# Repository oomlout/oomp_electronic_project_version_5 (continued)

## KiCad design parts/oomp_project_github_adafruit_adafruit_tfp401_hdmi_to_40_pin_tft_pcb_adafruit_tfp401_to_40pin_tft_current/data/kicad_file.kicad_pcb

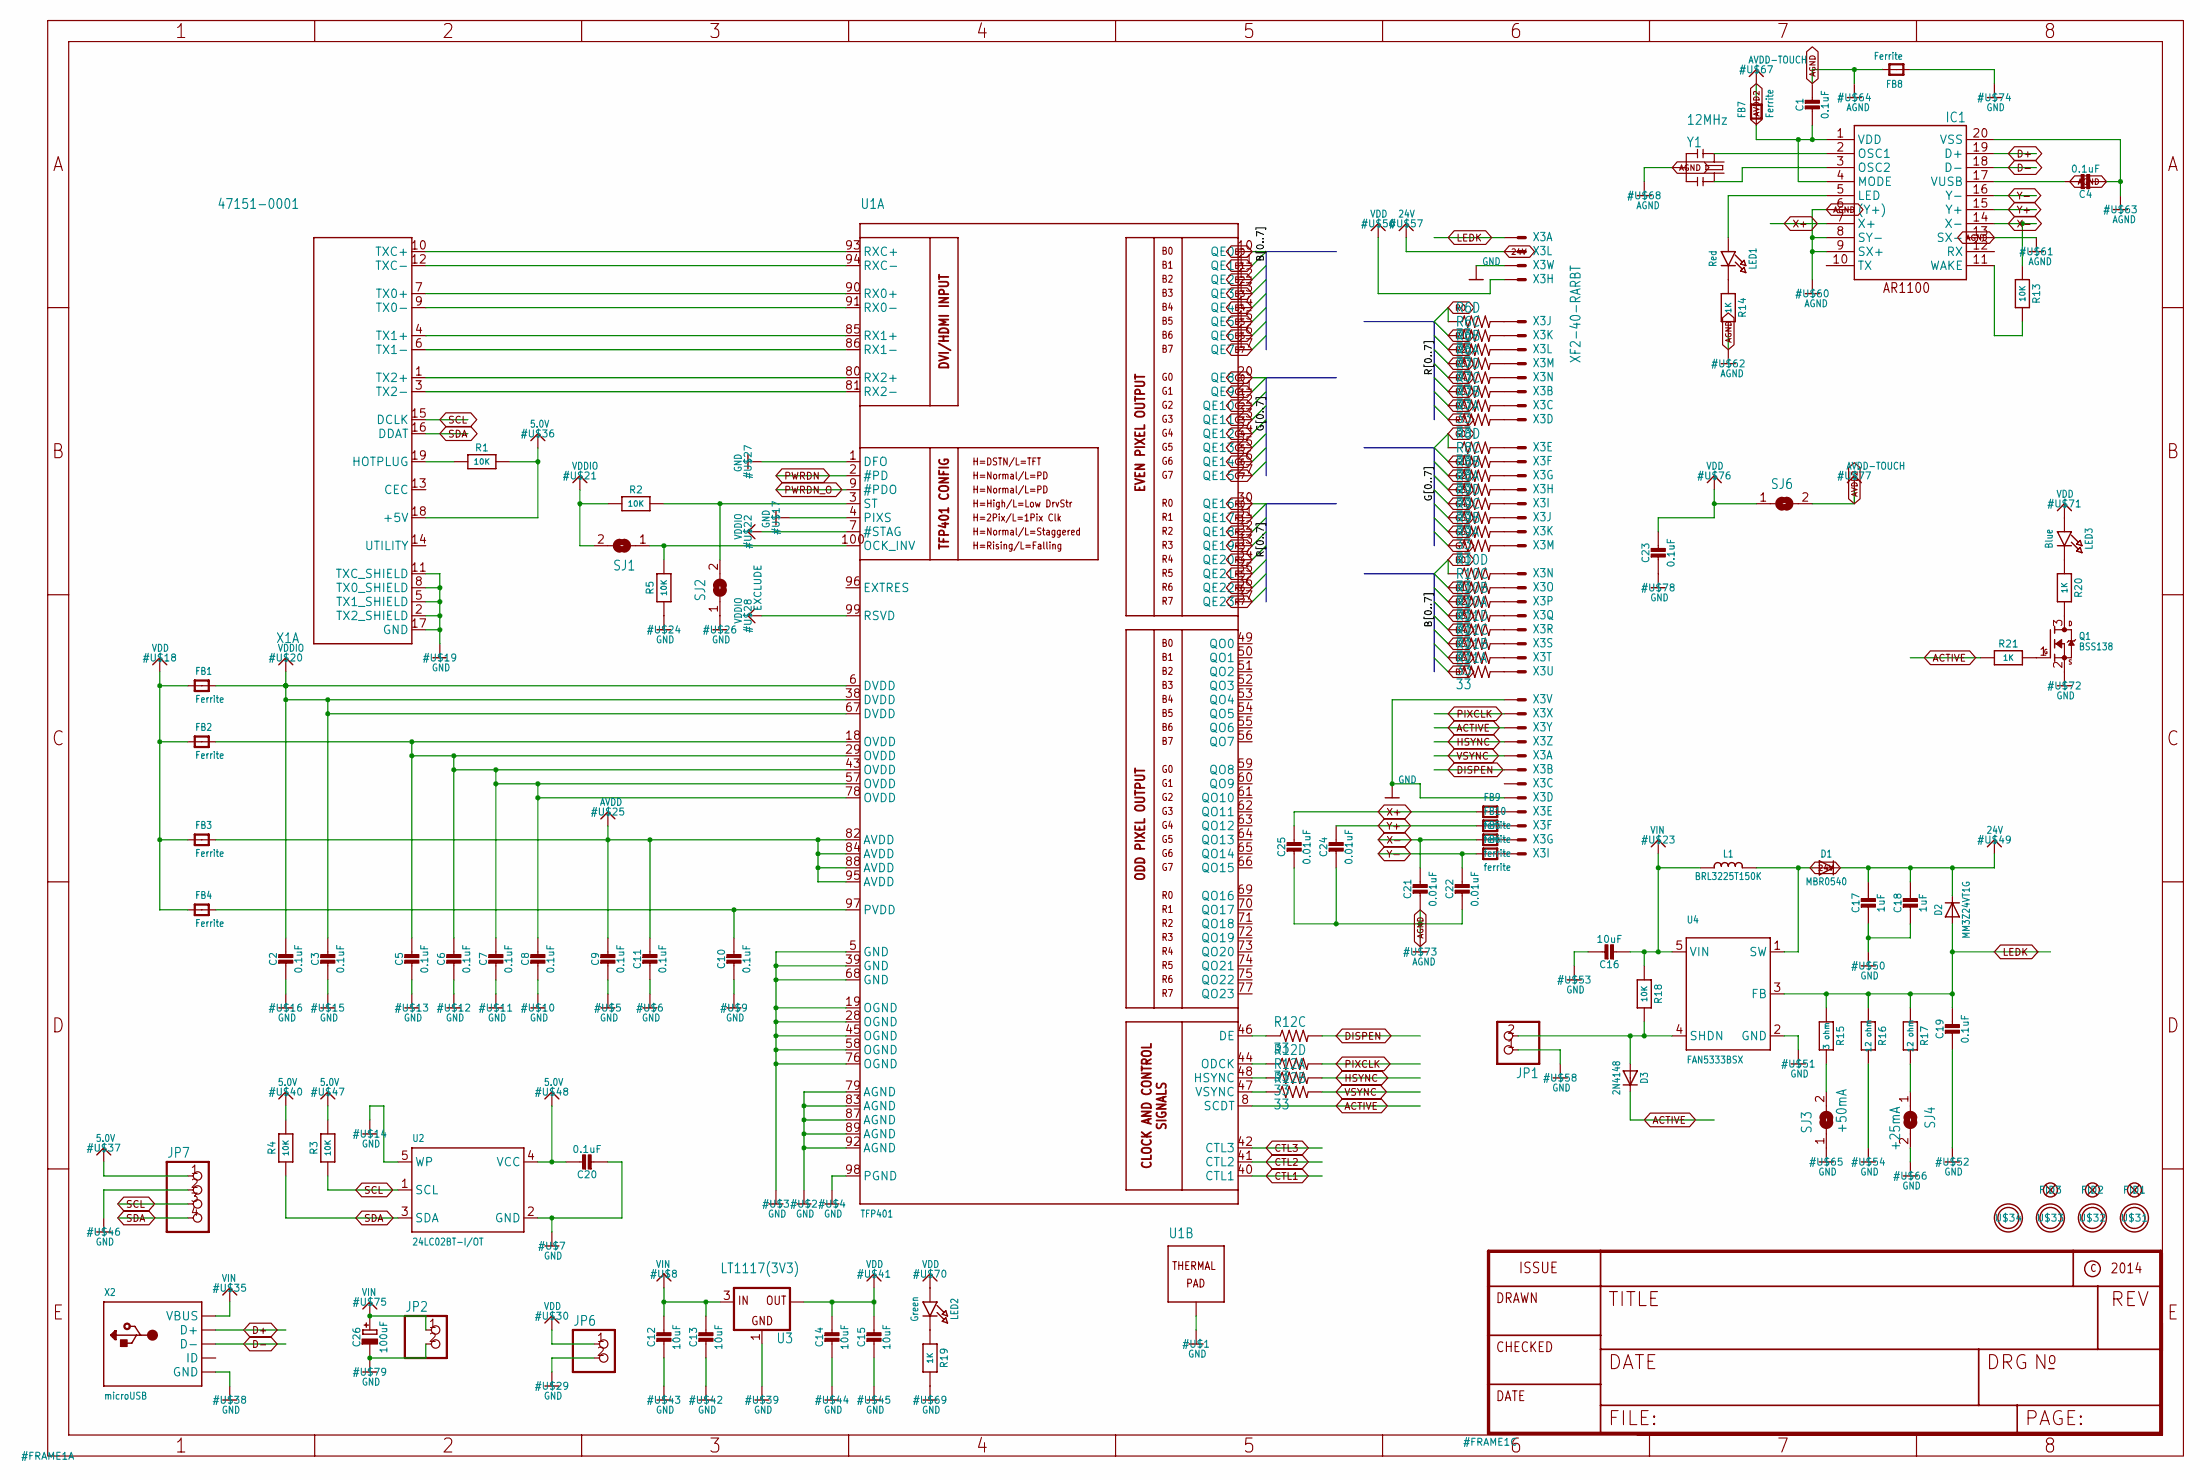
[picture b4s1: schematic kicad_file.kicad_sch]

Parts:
C1, C2, C3, C4, C5, C7, C8, C9, C10, C11, C19, C20, C23: 0.1uF; 0805-NO
C6: 0.1uF; _0805MP
C12, C13, C14, C15, C16: 10uF; 0805-NO
C17, C18: 1uF; 0805-NO
C21, C22, C24, C25: 0.01uF; 0805-NO
C26: 100uF; PANASONIC_C
D1: MBR0540; SOD-123
D2: MM3Z24VT1G; SMADIODE
D3: 2N4148; SOD-323
FB1, FB2, FB3, FB4, FB7, FB8: Ferrite; _0805MP
FB5, FB6, FB9, FB10: ferrite; _0805MP
FID1, FID2, FID3: FIDUCIAL""; FIDUCIAL_1MM
IC1: AR1100_SSOP; TSSOP20-5.3MMBODY
JP1, JP2, JP6: HEADER-1X2ROUND; 1X02_ROUND
JP7: HEADER-1X476MIL; 1X04_ROUND_76
L1: BRL3225T150K; INDUCTOR_5X5MM_NR5040_NOTHERMALS
LED1: Red; CHIPLED_0805_NOOUTLINE
LED2: Green; CHIPLED_0805_NOOUTLINE
LED3: Blue; CHIPLED_0805_NOOUTLINE
Q1: BSS138; SOT23-R
R1, R2, R3, R4, R18: 10K; 0805-NO
R5, R13: 10K; _0805MP
R6, R7, R8, R9, R10, R11, R12: 33; RESPACK_4X0603
R14, R19, R20, R21: 1K; 0805-NO
R15: 3 ohm; 0805-NO
R16, R17: 12 ohm; 0805-NO
SJ1, SJ2: SOLDERJUMPER; SOLDERJUMPER_ARROW_NOPASTE
SJ3: +50mA; SOLDERJUMPER_ARROW_NOPASTE
SJ4: +25mA; SOLDERJUMPER_ARROW_NOPASTE
SJ6: SOLDERJUMPERCLOSED; SOLDERJUMPER_CLOSEDWIRE
U1: TFP401; S-PQFP-G100
U2: 24LC02BT-I/OT; SOT23-5
U3: LT1117(3V3); SOT223-R
U4: FAN5333BSX; SOT23-5
U$31, U$32, U$33, U$34: MOUNTINGHOLE3.0; MOUNTINGHOLE_3.0_PLATED
X1: 47151-0001; HDMI_MOLEX_47151-0001_DIMLAYER
X2: microUSB; 4UCONN_20329
X3: XF2-40-RARBT; 4-1734839-0
Y1: 12MHz; RESONATOR-SMD

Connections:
5.0V: C20.1, JP7.1, R1.2, R3.2, R4.2, U2.4 (VCC), X1.18 (+5V)
24V: C17.1, C18.1, D1.C, D2.C, X3.2 (MS)
ACTIVE: D3.C, R21.1, U1.8 (SCDT), X3.31 (MS)
AGND: C1.1, C4.2, C21.2, C22.2, C24.2, C25.2, FB8.2, IC1.6 ((Y+)), IC1.8 (SY-), IC1.9 (SX+), IC1.13 (SX-), IC1.20 (VSS), R14.2, Y1.2
ASD: R12.3 (1), U1.46 (DE)
AVDD: C9.1, C11.1, FB3.2, U1.82 (AVDD), U1.84 (AVDD), U1.88 (AVDD), U1.95 (AVDD)
AVDD2: FB7.2, SJ6.2
B0: R10.4 (1), U1.10 (QE0)
B1: R10.3 (1), U1.11 (QE1)
B2: R10.2 (1), U1.12 (QE2)
B3: R10.1, U1.13 (QE3)
B4: R11.4 (1), U1.14 (QE4)
B5: R11.3 (1), U1.15 (QE5)
B6: R11.2 (1), U1.16 (QE6)
B7: R11.1, U1.17 (QE7)
CTL1: U1.40 (CTL1)
CTL2: U1.41 (CTL2)
CTL3: U1.42 (CTL3)
CVB: R12.2 (1), U1.47 (VSYNC)
D+: IC1.19 (D+), X2.D+
D-: IC1.18 (D-), X2.D-
DISPEN: R12.6 (2), X3.34 (MS)
G0: R8.4 (1), U1.20 (QE8)
G1: R8.3 (1), U1.21 (QE9)
G2: R8.2 (1), U1.22 (QE10)
G3: R8.1, U1.23 (QE11)
G4: R9.4 (1), U1.24 (QE12)
G5: R9.3 (1), U1.25 (QE13)
G6: R9.2 (1), U1.26 (QE14)
G7: R9.1, U1.27 (QE15)
GND: C2.2, C3.2, C5.2, C6.2, C7.2, C8.2, C9.2, C10.2, C11.2, C12.2, C13.2, C14.2, C15.2, C16.1, C17.2, C18.2, C19.2, C20.2, C23.2, C26.-, FB8.1, JP1.1, JP2.2, JP6.2, JP7.2, Q1.2 (S), R5.1, R16.2, R19.2, SJ2.1, SJ3.1, SJ4.2, U1.1 (DFO), U1.4 (PIXS), U1.5 (GND), U1.19 (OGND), U1.28 (OGND), U1.39 (GND), U1.45 (OGND), U1.58 (OGND), U1.68 (GND), U1.76 (OGND), U1.79 (AGND), U1.83 (AGND), U1.87 (AGND), U1.89 (AGND), U1.92 (AGND), U1.98 (PGND), U1.P$1 (TP), U1.P$2 (TP), U1.P$3 (TP), U1.P$4 (TP), U1.P$5 (TP), U1.P$6 (TP), U1.P$7 (TP), U1.P$8 (TP), U1.P$9 (TP), U1.P$10 (TP), U1.P$11 (TP), U1.P$12 (TP), U1.P$13 (TP), U1.P$14 (TP), U1.P$15 (TP), U1.P$16 (TP), U1.THERMAL (TP), U2.2 (GND), U2.5 (WP), U3.1 (GND), U4.2 (GND), X1.2 (TX2_SHIELD), X1.5 (TX1_SHIELD), X1.8 (TX0_SHIELD), X1.11 (TXC_SHIELD), X1.17 (GND), X1.P$1 (GND), X1.P$2 (GND), X1.P$3 (GND), X1.P$4 (GND), X2.BASE@1 (GND), X2.BASE@2 (GND), X2.GND, X2.SPRT@1 (GND), X2.SPRT@2 (GND), X2.SPRT@3 (GND), X2.SPRT@4 (GND), X3.3 (MS), X3.29 (MS), X3.36 (MS)
HSYNC: R12.8 (2), X3.32 (MS)
LEDK: C19.1, D2.A, R15.1, R16.1, R17.1, U4.3 (FB), X3.1 (MSV)
unnamed: U1.93 (RXC+), X1.10 (TXC+)
unnamed: U1.94 (RXC-), X1.12 (TXC-)
unnamed: U1.90 (RX0+), X1.7 (TX0+)
unnamed: U1.91 (RX0-), X1.9 (TX0-)
unnamed: U1.85 (RX1+), X1.4 (TX1+)
unnamed: U1.86 (RX1-), X1.6 (TX1-)
unnamed: U1.80 (RX2+), X1.1 (TX2+)
unnamed: U1.81 (RX2-), X1.3 (TX2-)
unnamed: R1.1, X1.19 (HOTPLUG)
unnamed: IC1.2 (OSC1), Y1.1
unnamed: IC1.3 (OSC2), Y1.3
unnamed: C4.1, IC1.17 (VUSB)
unnamed: LED2.C, R19.1
unnamed: R6.5 (2), X3.5 (MS)
unnamed: R6.6 (2), X3.6 (MS)
unnamed: R6.7 (2), X3.7 (MS)
unnamed: R6.8 (2), X3.8 (MS)
unnamed: R7.5 (2), X3.9 (MS)
unnamed: R7.6 (2), X3.10 (MS)
unnamed: R7.7 (2), X3.11 (MS)
unnamed: R7.8 (2), X3.12 (MS)
unnamed: R8.5 (2), X3.13 (MS)
unnamed: R8.6 (2), X3.14 (MS)
unnamed: R8.7 (2), X3.15 (MS)
unnamed: R8.8 (2), X3.16 (MS)
unnamed: R9.5 (2), X3.17 (MS)
unnamed: R9.6 (2), X3.18 (MS)
unnamed: R9.7 (2), X3.19 (MS)
unnamed: R9.8 (2), X3.20 (MS)
unnamed: R10.5 (2), X3.21 (MS)
unnamed: R10.6 (2), X3.22 (MS)
unnamed: R10.7 (2), X3.23 (MS)
unnamed: R10.8 (2), X3.24 (MS)
unnamed: R11.5 (2), X3.25 (MS)
unnamed: R11.6 (2), X3.26 (MS)
unnamed: R11.7 (2), X3.27 (MS)
unnamed: C10.1, FB4.2, U1.97 (PVDD)
unnamed: R11.8 (2), X3.28 (MS)
unnamed: IC1.11 (WAKE), R13.2
unnamed: LED1.C, R14.1
unnamed: C5.1, C6.1, C7.1, C8.1, FB2.2, U1.18 (OVDD), U1.29 (OVDD), U1.43 (OVDD), U1.57 (OVDD), U1.78 (OVDD)
unnamed: IC1.5 (LED), LED1.A
unnamed: LED3.C, R20.1
unnamed: Q1.3 (D), R20.2
unnamed: D1.A, L1.P$2 (2), U4.1 (SW)
unnamed: Q1.1 (G), R21.2
unnamed: R15.2, SJ3.2
unnamed: R17.2, SJ4.1
unnamed: D3.A, JP1.2, R18.2, U4.4 (SHDN)
unnamed: FB5.2, X3.39 (MS)
unnamed: FB6.2, X3.40 (MS)
unnamed: C1.2, FB7.1, IC1.1 (VDD), IC1.4 (MODE)
unnamed: FB9.2, X3.37 (MS)
unnamed: FB10.2, X3.38 (MS)
OCK_INV: R5.2, SJ1.1, U1.100 (OCK_INV)
PIXCLK: R12.5 (2), X3.30 (MS)
PWRDN: U1.2 (#PD)
PWRDN_O: U1.9 (#PDO)
R0: R6.4 (1), U1.30 (QE16)
R1: R6.3 (1), U1.31 (QE17)
R2: R6.2 (1), U1.32 (QE18)
R3: R6.1, U1.33 (QE19)
R4: R7.4 (1), U1.34 (QE20)
R5: R7.3 (1), U1.35 (QE21)
R6: R7.2 (1), U1.36 (QE22)
R7: R7.1, U1.37 (QE23)
SCL: JP7.3, R3.1, U2.1 (SCL), X1.15 (DCLK)
SDA: JP7.4, R4.1, U2.3 (SDA), X1.16 (DDAT)
ST: R2.2, SJ2.2, U1.3 (ST)
VDD: C14.1, C15.1, C23.1, FB1.1, FB2.1, FB3.1, FB4.1, JP6.1, LED2.A, LED3.A, SJ6.1, U3.2 (OUT), U3.4 (OUT), X3.4 (MS)
VDDIO: C2.1, C3.1, FB1.2, R2.1, SJ1.2, U1.6 (DVDD), U1.7 (#STAG), U1.38 (DVDD), U1.67 (DVDD), U1.99 (RSVD)
VIN: C12.1, C13.1, C16.2, C26.+, JP2.1, L1.P$1 (1), R18.1, U3.3 (IN), U4.5 (VIN), X2.VBUS
VSYNC: R12.7 (2), X3.33 (MS)
X+: C25.1, FB9.1, IC1.7 (X+)
X-: C21.1, FB5.1, IC1.14 (X-), R13.1
XCV: R12.1, U1.48 (HSYNC)
Y+: C24.1, FB10.1, IC1.15 (Y+)
Y-: C22.1, FB6.1, IC1.16 (Y-)
ZXC: R12.4 (1), U1.44 (ODCK)

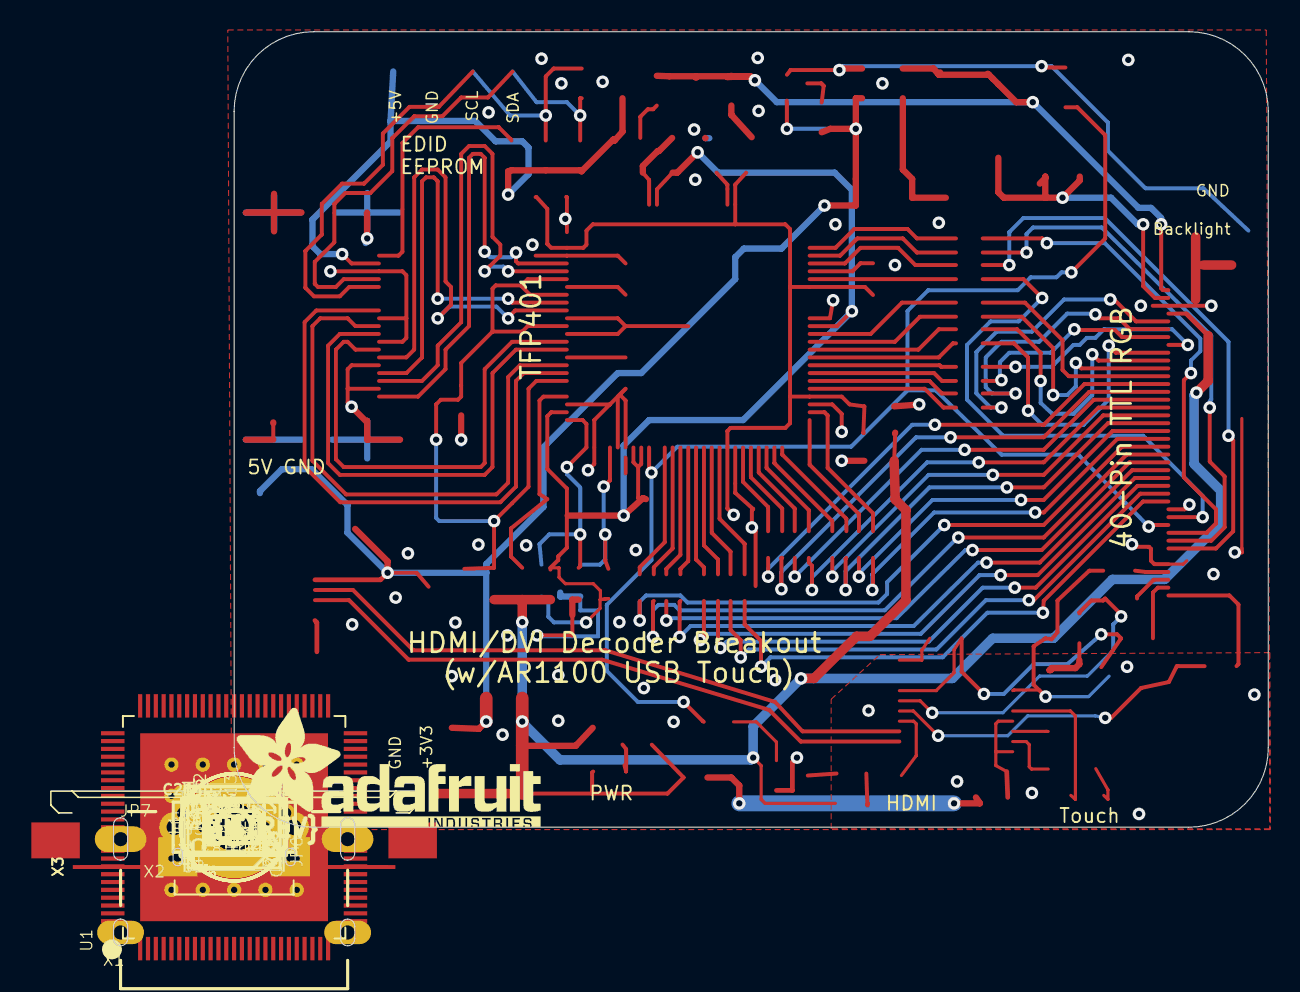
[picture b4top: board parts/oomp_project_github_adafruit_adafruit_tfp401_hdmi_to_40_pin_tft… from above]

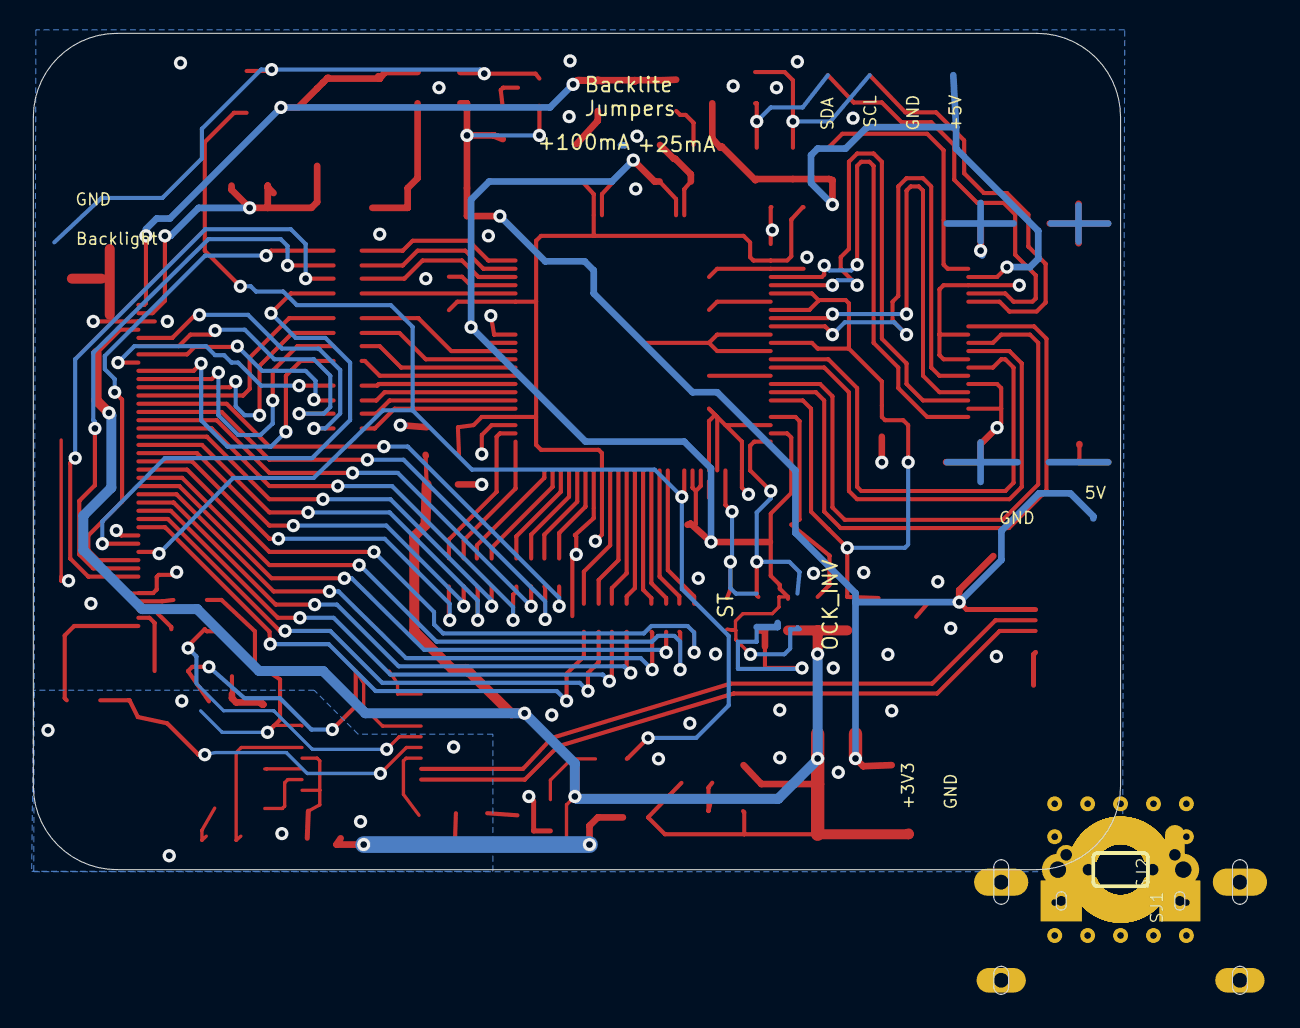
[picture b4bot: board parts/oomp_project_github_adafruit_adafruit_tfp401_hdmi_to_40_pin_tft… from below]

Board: 2 copper layers, 66.0 x 50.8 mm, 92 parts (2 on the bottom side), 107 nets.

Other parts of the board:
U$80: PCBFEAT-REV-056
U$81: ADAFRUIT_TEXT_20MM

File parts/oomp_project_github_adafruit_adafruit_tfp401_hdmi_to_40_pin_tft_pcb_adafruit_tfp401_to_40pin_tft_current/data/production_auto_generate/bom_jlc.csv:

Comment,Designator,Footprint,LCSC Part #
,"JP1,JP2,JP6",Adafruit TFP401 to 40pin TFT-import-fps:1X02_ROUND,C492401
,JP7,Adafruit TFP401 to 40pin TFT-import-fps:1X04_ROUND_76,C42431795
,U$81,Adafruit TFP401 to 40pin TFT-import-fps:ADAFRUIT_TEXT_20MM,
,U$80,Adafruit TFP401 to 40pin TFT-import-fps:PCBFEAT-REV-056,
0.01uF,"C21,C22,C24,C25",Adafruit TFP401 to 40pin TFT-import-fps:0805-NO,
0.1uF,"C1,C2,C3,C4,C5,C7,C8,C9,C10,C11,C19,C20,C23",Adafruit TFP401 to 40pin TFT-import-fps:0805-NO,
0.1uF,C6,Adafruit TFP401 to 40pin TFT-import-fps:_0805MP,
100uF,C26,Adafruit TFP401 to 40pin TFT-import-fps:PANASONIC_C,
10K,"R1,R2,R3,R4,R18",Adafruit TFP401 to 40pin TFT-import-fps:0805-NO,C17414
10K,"R5,R13",Adafruit TFP401 to 40pin TFT-import-fps:_0805MP,C17414
10uF,"C12,C13,C14,C15,C16",Adafruit TFP401 to 40pin TFT-import-fps:0805-NO,
12 ohm,"R16,R17",Adafruit TFP401 to 40pin TFT-import-fps:0805-NO,C2907226
12MHz,Y1,Adafruit TFP401 to 40pin TFT-import-fps:RESONATOR-SMD,
1K,"R14,R19,R20,R21",Adafruit TFP401 to 40pin TFT-import-fps:0805-NO,C17513
1uF,"C17,C18",Adafruit TFP401 to 40pin TFT-import-fps:0805-NO,
24LC02BT-I/OT,U2,Adafruit TFP401 to 40pin TFT-import-fps:SOT23-5,
2N4148,D3,Adafruit TFP401 to 40pin TFT-import-fps:SOD-323,
3 ohm,R15,Adafruit TFP401 to 40pin TFT-import-fps:0805-NO,
33,"R6,R7,R8,R9,R10,R11,R12",Adafruit TFP401 to 40pin TFT-import-fps:RESPACK_4X0603,C23140
47151-0001,X1,Adafruit TFP401 to 40pin TFT-import-fps:HDMI_MOLEX_47151-0001_DIMLAYER,
AR1100_SSOP,IC1,Adafruit TFP401 to 40pin TFT-import-fps:TSSOP20-5.3MMBODY,
Blue,LED3,Adafruit TFP401 to 40pin TFT-import-fps:CHIPLED_0805_NOOUTLINE,
BRL3225T150K,L1,Adafruit TFP401 to 40pin TFT-import-fps:INDUCTOR_5X5MM_NR5040_NOTHERMALS,
BSS138,Q1,Adafruit TFP401 to 40pin TFT-import-fps:SOT23-R,C52895
FAN5333BSX,U4,Adafruit TFP401 to 40pin TFT-import-fps:SOT23-5,
Ferrite,"FB1,FB2,FB3,FB4,FB7,FB8",Adafruit TFP401 to 40pin TFT-import-fps:_0805MP,
ferrite,"FB5,FB6,FB9,FB10",Adafruit TFP401 to 40pin TFT-import-fps:_0805MP,
Green,LED2,Adafruit TFP401 to 40pin TFT-import-fps:CHIPLED_0805_NOOUTLINE,
LT1117(3V3),U3,Adafruit TFP401 to 40pin TFT-import-fps:SOT223-R,
MBR0540,D1,Adafruit TFP401 to 40pin TFT-import-fps:SOD-123,
microUSB,X2,Adafruit TFP401 to 40pin TFT-import-fps:4UCONN_20329,
MM3Z24VT1G,D2,Adafruit TFP401 to 40pin TFT-import-fps:SMADIODE,
Red,LED1,Adafruit TFP401 to 40pin TFT-import-fps:CHIPLED_0805_NOOUTLINE,
TFP401,U1,Adafruit TFP401 to 40pin TFT-import-fps:S-PQFP-G100,
XF2-40-RARBT,X3,Adafruit TFP401 to 40pin TFT-import-fps:4-1734839-0,
